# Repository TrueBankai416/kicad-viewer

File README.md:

# KiCAD file Viewer for Nextcloud

## Building

### Dependencies

- POSIX preferred
- make
- whichcd
- php
- composer
- node (preferred via nvm)
- npm
- tar
- curl

### Prefligth

```sh
nvm use
npm install
```

### Building for prod

```sh
make
```

### Building for dev static

```sh
make dev
```

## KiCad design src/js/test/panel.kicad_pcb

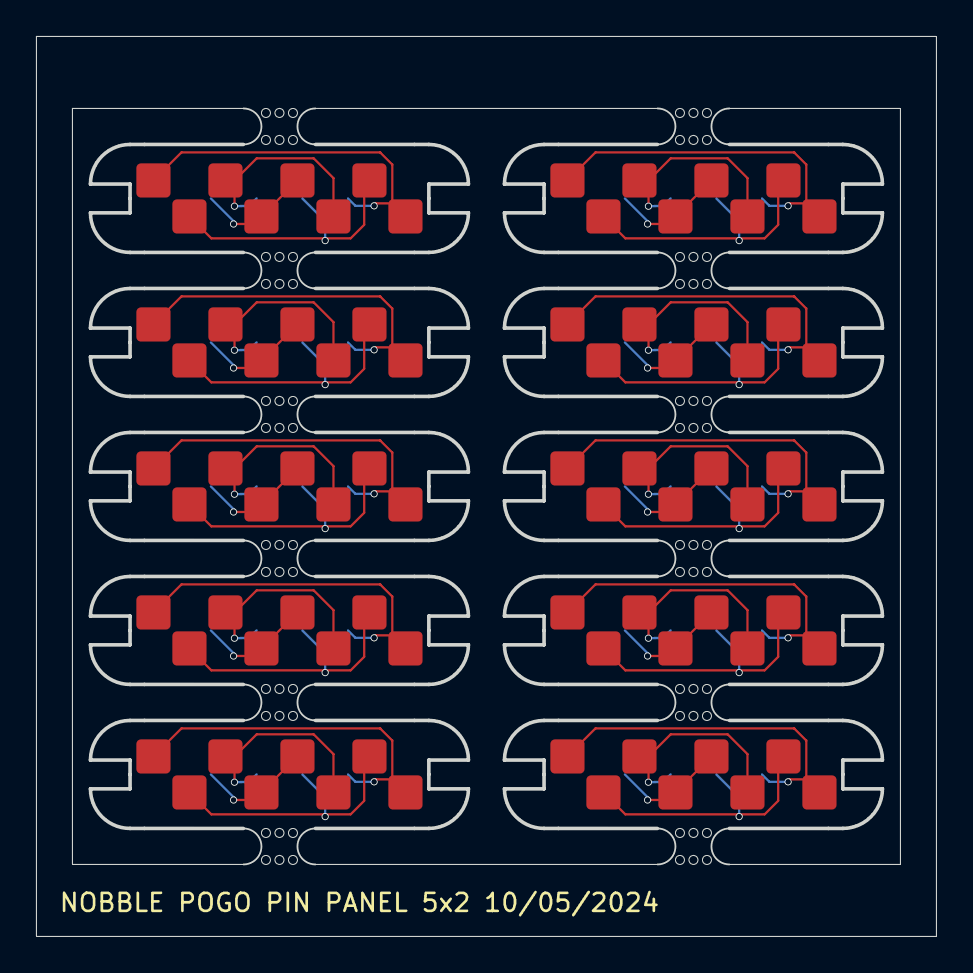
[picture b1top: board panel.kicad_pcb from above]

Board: 2 copper layers, 49.9 x 49.9 mm, 22 parts (0 on the bottom side), 4 nets.

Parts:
I2C_LANDING1, I2C_LANDING2, I2C_LANDING3, I2C_LANDING4, I2C_LANDING5, I2C_LANDING6, I2C_LANDING7, I2C_LANDING8, I2C_LANDING9, I2C_LANDING10: MODULE_I2C_SYM
mouse-bite-2mm-slot, mouse-bite-2mm-slot1, mouse-bite-2mm-slot2, mouse-bite-2mm-slot3, mouse-bite-2mm-slot4, mouse-bite-2mm-slot5, mouse-bite-2mm-slot6, mouse-bite-2mm-slot7, mouse-bite-2mm-slot8, mouse-bite-2mm-slot9, mouse-bite-2mm-slot10, mouse-bite-2mm-slot11: VAL**; mouse-bite-2mm-slot

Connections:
/NET1: I2C_LANDING1.1 (VCC), I2C_LANDING2.1 (VCC), I2C_LANDING3.1 (VCC), I2C_LANDING4.1 (VCC), I2C_LANDING5.1 (VCC), I2C_LANDING6.1 (VCC), I2C_LANDING7.1 (VCC), I2C_LANDING8.1 (VCC), I2C_LANDING9.1 (VCC), I2C_LANDING10.1 (VCC)
/NET2: I2C_LANDING1.2 (SDA), I2C_LANDING2.2 (SDA), I2C_LANDING3.2 (SDA), I2C_LANDING4.2 (SDA), I2C_LANDING5.2 (SDA), I2C_LANDING6.2 (SDA), I2C_LANDING7.2 (SDA), I2C_LANDING8.2 (SDA), I2C_LANDING9.2 (SDA), I2C_LANDING10.2 (SDA)
/NET3: I2C_LANDING1.3 (SCL), I2C_LANDING2.3 (SCL), I2C_LANDING3.3 (SCL), I2C_LANDING4.3 (SCL), I2C_LANDING5.3 (SCL), I2C_LANDING6.3 (SCL), I2C_LANDING7.3 (SCL), I2C_LANDING8.3 (SCL), I2C_LANDING9.3 (SCL), I2C_LANDING10.3 (SCL)
/NET4: I2C_LANDING1.4 (GND), I2C_LANDING2.4 (GND), I2C_LANDING3.4 (GND), I2C_LANDING4.4 (GND), I2C_LANDING5.4 (GND), I2C_LANDING6.4 (GND), I2C_LANDING7.4 (GND), I2C_LANDING8.4 (GND), I2C_LANDING9.4 (GND), I2C_LANDING10.4 (GND)

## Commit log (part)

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2025-05-28 Implement a simple HTTP server in Node.js for serving static files
    - Added a new file `serve.js` that creates an HTTP server using Node.js.
    - The server listens on port 8080 and serves files from the current directory.
    - Implemented MIME type handling for various file extensions.
    - Added error handling for file not found and server errors.
    Add Composer autoload files and dependencies
    - Generated `autoload.php`, `ClassLoader.php`, and related files for Composer autoloading.
2025-05-28 Add README.md with build instructions and dependencies
2025-05-28 Clean up: Build files are not included in the commits anymore.
2025-05-28 Add app creation script with dependency checking
    Created a comprehensive setup script that automates the build process for the KiCAD Viewer Nextcloud app:
    **New files:**
    - `requirements.txt`: Lists all system dependencies needed to build the app
    - `setup.sh`: Interactive script that checks dependencies, installs npm packages, and builds the app
    **Key features:**
    - ✅ Checks all system dependencies from requirements.txt
2025-05-28 Add detailed debugging to identify DOMException source
    Added comprehensive error handling and logging throughout the `initKiCanvas` method to pinpoint exactly where the DOMException is occurring. This includes:
    - Detailed logging for kicanvas-source element creation
    - Error handling for each attribute setting operation
    - Granular logging in loadContentIntoKiCanvas method
    - Better error tracking for appendChild operations
    This will help identify the specific operation causing the "Operation is not supported" DOMException.
2025-05-28 Avoid DOMException by using innerHTML to create kicanvas-source
    Completely rewrote the `createKiCanvasSourceElement` method to avoid the DOMException that occurs when using `document.createElement('kicanvas-source')`.
    **The Problem:** Custom elements like `kicanvas-source` have restrictions on programmatic creation that cause DOMExceptions.
    **The Solution:**
    - Use innerHTML to create the element as an HTML string instead of createElement
    - Try multiple content embedding approaches in order of reliability:
    1. **Blob URL** (most reliable for KiCanvas)
2025-05-28 Switch to File object approach for better filename preservation
    **Fixed the KiCanvas filename detection issue:**
    **Problem:** KiCanvas was misinterpreting data URLs - it saw `x-kicad-schematic;base64,...` as the filename instead of recognizing the proper file type.
    **Solution:**
    - **Use File objects instead of Blobs** - this preserves the actual filename
    - **Remove data URL approach** - was causing filename parsing issues
    - **Create proper File object**: `new File([content], filename, {type: mimeType})`
2025-05-28 Fix generateUrl import for server endpoint URLs
    **Simple fix for the `generateUrl is not defined` error:**
    - Added `generateUrl` import from `@nextcloud/router` alongside the existing `generateFilePath` import
    - This enables proper URL generation for our server endpoint: `/apps/kicad_viewer/api/file/{path}/{filename}`
    **Expected result:** The server endpoint approach should now work without the ReferenceError, and we should see the proper endpoint URLs being generated for KiCanvas to load files with correct filena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
    **Next step:** Test to see if KiCanvas can now recognize file types from the server endpoint URLs! 🎯
2025-05-29 Simplify controller for debugging route registration
    **Debugging approach - simplified controller to test basic routing:**
    1. **Removed manual controller registration** - modern Nextcloud should auto-discover controllers
    2. **Simplified FileController** to return basic JSON response instead of file content
    3. **Removed complex dependencies** (IRootFolder, IUserSession) that might cause issues
    **Test steps:**
    1. Disable/enable app: `php occ app:disable kicad_viewer && php occ app:enable kicad_viewer`
2025-05-29 Restore file-serving functionality to controller
    **The final fix! Controller now serves actual KiCAD file content instead of test JSON:**
    **Key changes:**
    - Restored `IRootFolder` and `IUserSession` dependencies for file access
    - Changed from `DataResponse` to `StreamResponse` to serve file content
    - Removed `@PublicPage` annotation (requires authentication to access user files)
    - Added proper MIME type and headers for KiCanvas
2025-05-29 Add simple test route to debug routing system
    **Diagnostic approach to identify routing issue:**
    **Added simple test route:**
    - URL: `/apps/kicad_viewer/test`
    - Maps to: `FileController->test()`
    - Returns: "Hello from KiCAD Viewer!"
    - Uses `@PublicPage` (no authentication required)
2025-05-29 Simplify Application.php - remove IBootstrap to fix route registration
    **Major architectural change to fix bootstrap issues:**
    **Removed IBootstrap interface completely:**
    - The RuntimeException showed IBootstrap wasn't working properly
    - "App class...is not setup via query() but directly" indicates bootstrap system failure
    - Many Nextcloud apps work without IBootstrap
    **Simplified to basic App class:**
2025-05-29 Simplify Application to follow official Nextcloud tutorial pattern
    **CRITICAL CHANGE: Remove IBootstrap to enable automatic route loading**
    **Following the official Nextcloud app-tutorial pattern:**
    - ✅ **Simple App class** (no IBootstrap interface)
    - ✅ **Const APP_ID** pattern
    - ✅ **Direct event listener registration** in constructor
    - ✅ **Should enable automatic routes.php loading**
2025-05-29 Fix missing namespace in routes.php and update version compatibility
    **CRITICAL FIXES for route loading issues:**
    **1. Added missing namespace to routes.php:**
    ```php
    namespace OCA\kicad_viewer\AppInfo;
    ```
    Core Nextcloud apps all have this namespace declaration - this could be why our routes weren't being discovered.
2025-05-29 Add debug logging to check KiCanvas DOM attributes
    **DEBUG: Check what KiCanvas actually receives from Vue reactive bindings**
    **Issue:** KiCanvas creates blob URL correctly but still reports "unknown file type"
    - Blob URL: `blob:...9d7d6154-ac67-4ecf-8120-db91dea96945` ✅
    - File content: 20KB ✅
    - Vue properties: filename, type, format set ✅
    - But KiCanvas can't detect file type ❌
2025-05-29 Eliminate ALL Vue reactivity for KiCanvas - use pure DOM manipulation
    **CRITICAL FIX: Remove all Vue reactive properties to completely avoid DOMPurify**
    **Root cause:** ANY Vue reactive property assignment triggers DOMPurify sanitization.
    **Solution - Pure DOM approach:**
    - ✅ **Removed all reactive properties:** `kicanvasContent`, `kicanvasType`, `kicanvasFormat`
    - ✅ **Removed all Vue bindings:** No `:name`, `:type` in template
    - ✅ **Pure DOM manipulation:** `setAttribute()` and `textContent` only
2025-05-29 Add multiple KiCanvas refresh methods to force content recognition
    **AGGRESSIVE REFRESH: Try multiple approaches to make KiCanvas recognize loaded content**
    **Issue:** KiCanvas says "No valid sources specified" despite perfect DOM structure with 20KB content.
    **Root cause:** KiCanvas initializes immediately when created but may not re-scan for content added later.
    **Solution - Multiple refresh approaches:**
    1. ✅ **Standard update()** - Normal refresh method
    2. ✅ **connectedCallback()** - Force re-initialization lifecycle
2025-05-30 Fix KiCanvas loading loop issue
    This commit resolves the infinite loading spinner problem when opening KiCad files in Nextcloud.
    **Changes made:**
    1. **Improved async flow**: Converted `initKiCanvas()` to use proper async/await instead of nested setTimeout and $nextTick callbacks that could fail silently
    2. **Enhanced error handling**: Added `showErrorAndStopLoading()` method that ensures the loading spinner always stops, even when errors occur
    3. **Simplified content loading**: Refactored content loading into separate, testable methods (`tryBlobUrl`, `tryTextContent`, `tryDataUrl`, `tryDirectContent`) that are attempted sequentially
    4. **Guaranteed state management**: Every error path
2025-05-30 Add Vue reactivity debugging and manual DOM fallback
    Vue's v-show directives aren't updating properly despite isLoading state changes. Added:
    1. **Detailed DOM state logging** - Shows exact style attributes and display values
    2. **Force Vue update** - Uses $forceUpdate() to force reactivity
    3. **Manual DOM fallback** - Directly sets display styles if Vue fails
    4. **Better debugging** - Tracks before/after states of both elements
    This addresses the core issue where Vue reactivity appears broken, possibly due to the DOMException errors interfering with normal Vue operation.
2025-05-30 Remove kicanvas-source child element to match documentation
    **Final fix!** The KiCanvas documentation shows the embed element should be empty when using the `src` attribute:
    **Documentation pattern:**
    ```html
    <kicanvas-embed src="file.kicad_sch" controls="basic"></kicanvas-embed>
    ```
    **Our template now matches exactly:**
2025-05-30 Use original file URL directly - bypass all CSP issues
    **The simplest solution!** 🎯
    Instead of fetching content and converting to blob/data URLs (blocked by CSP), just set the original file URL directly as the `src` attribute.
    **Why this should work:**
    - ✅ **No CSP restrictions** on real HTTP URLs
    - ✅ **URL already works** (our fetch succeeds)
    - ✅ **Matches documentation pattern** exactly
2025-05-30 Fix filename path for API route - remove leading slash
    **Found the issue!** The filename had a leading slash that was getting URL encoded as `%2F`, causing the route to not match.
    **Problem:**
    ```
    filename: "/smart_cancrusher.kicad_sch"
    URL: /apps/kicad_viewer/api/file/public/%2Fsmart_cancrusher.kicad_sch ❌
    ```
2025-05-30 Fix KiCanvas src to use blob URL instead of direct content
    **Found the root cause!** 🎯
    KiCanvas expects a **URL/filename** in the `src` property, not file content. When we set content directly, it tried to parse it as a URL, causing encoding errors.
    **Solution:**
    - Create `Blob` from file content with proper MIME type
    - Generate `blob:` URL using `URL.createObjectURL()`
    - Set blob URL as `src` property
2025-05-30 Add filename parameter to data URL for KiCanvas file type recognition
    **Found the URL parsing issue!** KiCanvas was treating the MIME type as the filename:
    **Problem:**
    ```
    data:application/x-kicad-schematic;charset=utf-8,(content...)
    → KiCanvas sees: "x-kicad-schematic;charset=utf-8" as filename
    → Can't determine file type
2025-05-30 Fix loading spinner visibility by targeting correct Vue elements
    **Final fix for the loading spinner issue!** 🎯
    **Problem:** Vue loading spinner wasn't hiding even though `isLoading = false` was set correctly. The manual DOM manipulation wasn't finding the correct elements because they use CSS module classes.
    **Solution:**
    ✅ **Target elements via UUID container** - `document.querySelector(`#${this.uuid}`)`
    ✅ **Find loading element by CSS module pattern** - `div[class*="loadingContainer"]`
    ✅ **Force hide with multiple CSS properties** - both `display: none` and `visibility: hidden`
2025-05-30 Disable KiCanvas's own loading UI and hide its loading elements
    **Finally targeting the RIGHT loading spinner!** 🎯
    **Discovery:** The persistent loading spinner was from **KiCanvas itself**, not our Vue app. Our app's spinner was already hidden correctly.
    **Root Cause:** KiCanvas shows its own internal loading UI when it can't load certain resources due to CSP restrictions.
    **Solution:**
    **JavaScript - Disable KiCanvas Loading UI:**
    ```javascript
